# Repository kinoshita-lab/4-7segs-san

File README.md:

# 4-7segs-san kit

[Document in Japanese](README_ja.md)

4-7segs-san is a handy PCB with 4-digit 7-segment LEDs with decimal point.
You can speed up your MCU project with displaying numbers such as BPM, Level, etc.

## Main Features

- Only 2 GPIO pins required, connected to built in LED Driver(TM1640)
- Compatible for both 5V and 3.3V with builting buffers for signal,  DC-DC converter for power sourcing.
- Easy to use with [dedicated Arduino library for TM1640](./soft/4-7segs-san/TM1640.h)

## Kit Contents

- Pre-assembled circuit board
- [4 digit common cathode segment display](https://www.lcsc.com/product-detail/_Shenzhen-Zhihao-Elec-_C54396.html)
- 1x4 pin socket

## How to assemble

1. Cut all the pins on LED display to approx. 5mm for easier handling.
2. Solder the LED display and pin socket

## Sample program

Please refer to the [soft/4-7segs-san](soft/4-7segs-san)

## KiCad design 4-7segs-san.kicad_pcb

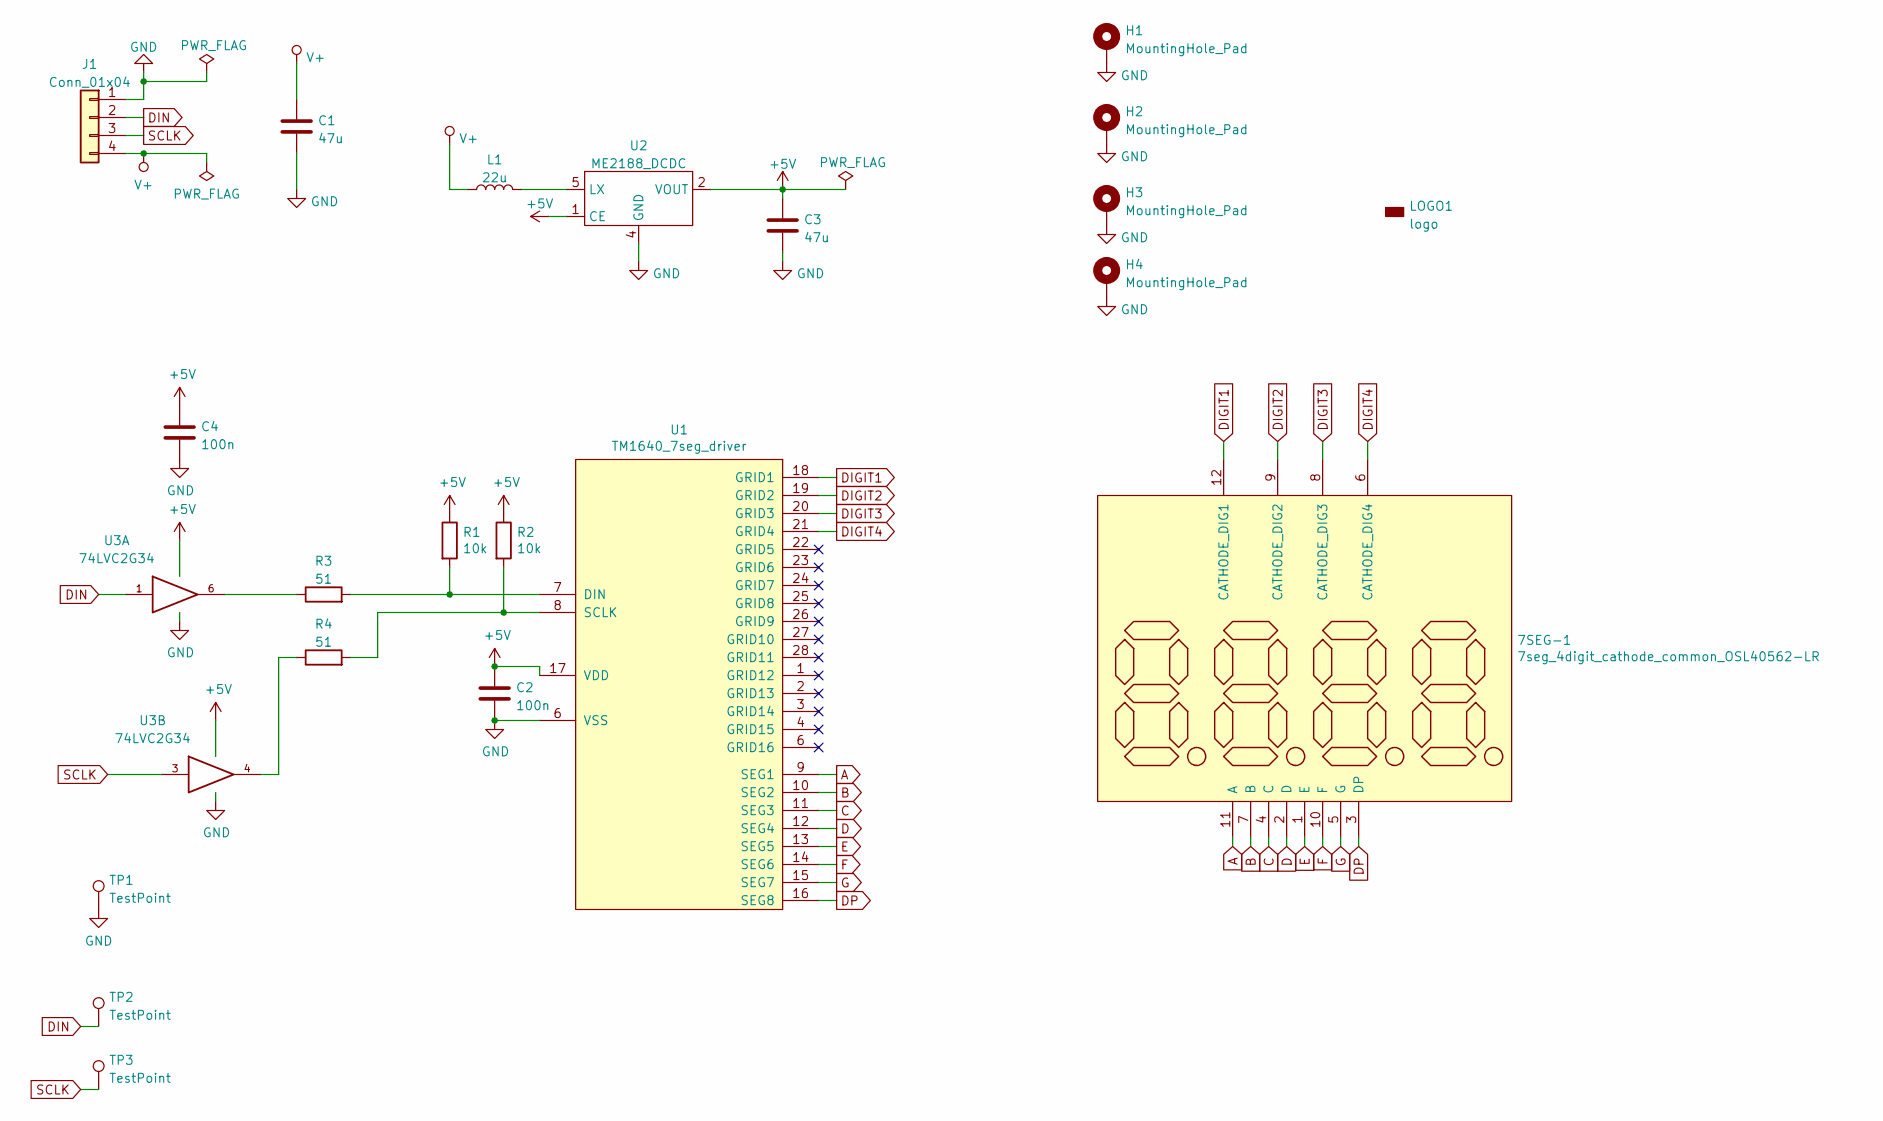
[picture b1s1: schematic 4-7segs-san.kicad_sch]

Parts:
7SEG-1: 7seg_4digit_cathode_common_OSL40562-LR; LCSC C54396
C1, C3: 47u; C_0805_2012Metric_Pad1.18x1.45mm_HandSolder; LCSC C16780
C2, C4: 100n; C_0402_1005Metric; LCSC C1525
H1, H2, H3, H4: MountingHole_Pad; MountingHole_3.2mm_M3_DIN965_Pad
J1: Conn_01x04; PinHeader_1x04_P2.54mm_Vertical; LCSC C5116530
L1: 22u; R_1210_3225Metric_Pad1.30x2.65mm_HandSolder; LCSC C223225
LOGO1: logo; kinoshita-logo_simplified_600dpi
R1, R2: 10k; R_0402_1005Metric_Pad0.72x0.64mm_HandSolder; LCSC C25744
R3, R4: 51; R_0402_1005Metric_Pad0.72x0.64mm_HandSolder; LCSC C25125
TP1, TP2, TP3: TestPoint; TestPoint_THTPad_D2.0mm_Drill1.0mm
U1: TM1640_7seg_driver; SOIC-28W_7.5x18.7mm_P1.27mm; LCSC C41327
U2: ME2188_DCDC; SOT-23-5_HandSoldering; LCSC C236768
U3: 74LVC2G34; SOT-23-6_Handsoldering; LCSC C347589

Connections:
+5V: C2.1, C3.1, C4.1, R1.1, R2.1, U1.17 (VDD), U2.1 (CE), U2.2 (VOUT), U3.5 (VCC)
A: 7SEG-1.11 (A), U1.9 (SEG1)
B: 7SEG-1.7 (B), U1.10 (SEG2)
C: 7SEG-1.4 (C), U1.11 (SEG3)
D: 7SEG-1.2 (D), U1.12 (SEG4)
DIGIT1: 7SEG-1.12 (CATHODE_DIG1), U1.18 (GRID1)
DIGIT2: 7SEG-1.9 (CATHODE_DIG2), U1.19 (GRID2)
DIGIT3: 7SEG-1.8 (CATHODE_DIG3), U1.20 (GRID3)
DIGIT4: 7SEG-1.6 (CATHODE_DIG4), U1.21 (GRID4)
DIN: J1.2, TP2.1, U3.1
DP: 7SEG-1.3 (DP), U1.16 (SEG8)
E: 7SEG-1.1 (E), U1.13 (SEG5)
F: 7SEG-1.10 (F), U1.14 (SEG6)
G: 7SEG-1.5 (G), U1.15 (SEG7)
GND: C1.2, C2.2, C3.2, C4.2, H1.1, H2.1, H3.1, H4.1, J1.1, TP1.1, U1.6 (VSS), U2.4 (GND), U3.2 (GND)
unnamed: L1.2, U2.5 (LX)
unnamed: R1.2, R3.2, U1.7 (DIN)
unnamed: R2.2, R4.2, U1.8 (SCLK)
unnamed: R3.1, U3.6
unnamed: R4.1, U3.4
SCLK: J1.3, TP3.1, U3.3
VCC1: C1.1, J1.4, L1.1

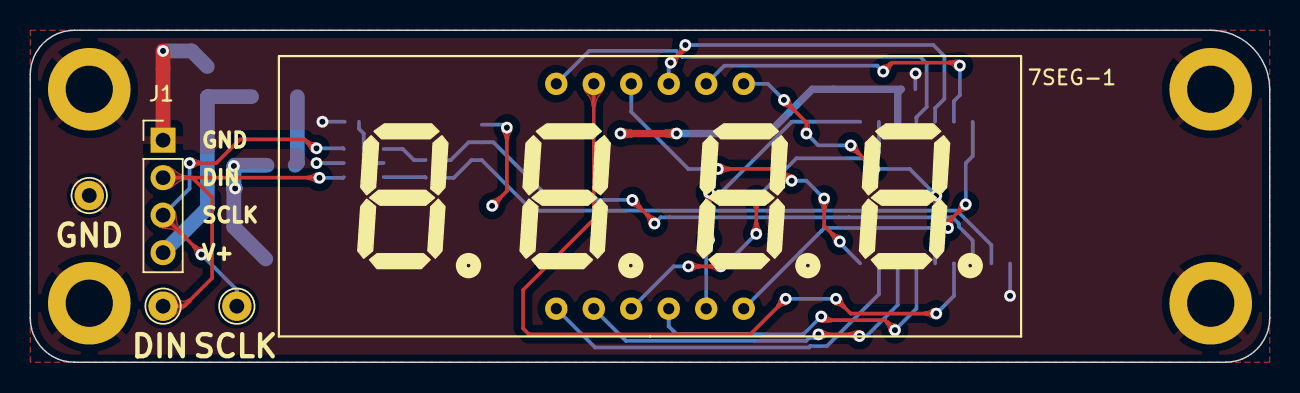
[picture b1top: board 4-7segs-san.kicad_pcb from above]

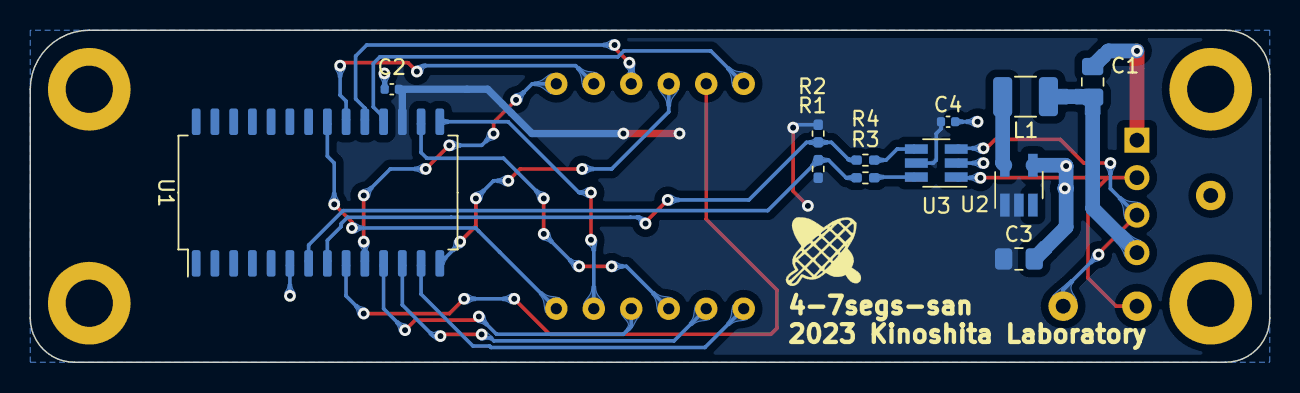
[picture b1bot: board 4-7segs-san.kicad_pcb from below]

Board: 2 copper layers, 84.0 x 22.5 mm, 22 parts (13 on the bottom side), 22 nets.

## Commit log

2023-03-17 revision 20220317 w/ software library(WIP)
2023-03-17 add empty readme
2023-03-17 add license
2023-03-17 add docs
2023-03-25 [soft] update TM1640 library
2023-03-25 [soft] update example
